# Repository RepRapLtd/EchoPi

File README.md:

# EchoPi

This is a device that uses the Raspberry Pi Zero as a WeMo device to turn on mains-powered items in your home using the Amazon Echo/Echo-Dot and their Alexa voice-recognition system.

## Safety

This uses mains electricity.  Mains will kill you if you touch it.  So don't.

The maximum current that this can switch is 1 amp.  With 220-volt mains that means a maximum 200W load; with 110-volt mains that means a maximum 100 W load.  The device is designed with a fuse holder.  Fit this with a 1 A fuse.

Parents: we set no age limits here - there are twelve-year-olds who could have organised D-Day, and there are thirty-seven-year-olds who can't be trusted with a penknife.  But don't let your children experiment with this unless you are confident that they are responsible and sensible.

Realistically, you will probably want to operate this with the cover off when you are setting it up.  Plug everything in to a disconnected extension cable and connect everything up.  Then - without touching anything to do with the uncovered case - plug the extension into a wall socket and turn it on.  Turn off and unplug the wall socket before you touch anything again.

## Electronics

The Eagle (https://cadsoft.io/) circuit design is single sided with a few jumpers.  It is intended to be produced by milling, though you can etch it conventionally as well of course.

The device incorporates a mains USB charger (like this: https://www.amazon.co.uk/Quality-Charger-Blackberry-Love-Accessories/dp/B01M2XE8V9/ ; red in the picture above).  This both acts as the plug so the device can be plugged into a wall socket, and as a 5V supply for the Raspberry Pi Zero and the rest of the electronics.

You will have to hack the charger by attaching wires to the three mains connections inside and drilling holes to run them out of.  The neutral and earth run straight through the device to the mains output, and the live wire goes through the fuse and then the opto-isolated phototriac, which switches it on and off.   

## Mechanics

The FreeCAD (http://www.freecadweb.org/) case is designed to be 3D printed.  

## Software

See here to create a linux image on an SD card for the Pi Zero:

https://www.raspberrypi.org/documentation/installation/installing-images/linux.md

Boot up the Pi Zero.  Change it's name to something you want:

http://www.howtogeek.com/167195/how-to-change-your-raspberry-pi-or-other-linux-devices-hostname/

Set your timezone:

http://www.geeklee.co.uk/update-time-zone-on-raspberry-pi-with-raspbian/

Set your Pi to have a static IP address, giving it the same one for ethernet and WiFi (you're not going to use both at once):

https://www.modmypi.com/blog/how-to-give-your-raspberry-pi-a-static-ip-address-update

Setup your WiFi network and password:

https://learn.adafruit.com/adafruits-raspberry-pi-lesson-3-network-setup/setting-up-wifi-with-occidentalis

Next get and run the EchoPi software:

$ git clone https://github.com/RepRapLtd/EchoPi.git

$ cd EchoPi/Software

$ pip install -r requirements.txt

$ nohup python echopi.py > /dev/null &

Tell Alexa, "Alexa, discover my devices."

Say, "Alexa, turn off device," and, "Alexa device on," to switch the mains socket off and on.

The line in the Python echopi.py program that sets the Alexa name of the device is this one:

     TRIGGERS = {"device": 52000}

Change the "device" to any name you like, but it's best to choose easily-pronounceable dictionary words or well-known proper nouns.  That way the Alexa speech recognition will be most reliable.

This is intended to connect to your home network using WiFi, but (particularly with BT HomeHubs) getting your Echo/Echo-Dot to find the device can be tricky.  

Start by turning off all the annoying "features" of the BT hub: disable Smart Setup; don't synchronise 5 GHz WiFi with 2.4 GHz (keep the passwords the same, though, or you'll never remember, and ignore the password warning it gives you when you do this); turn off Extended UPnP security.

Then use a micro-USB-to-ether adapter to connect the Pi Zero by wire to your hub.  

Run the Python program and tell Alexa to discover your devices.  She should find "device" (or whatever you have called it).  Test that it works by turning the load on and off.

Then shut everything down and disconnect it.  Fit a micro-USB-WiFi adapter in place of the Ethernet and power everything up again.  You should be able to ssh into the Pi as before.

Ask Alexa to turn your device on.  If she sees it, great.  But if not, press and hold the Echo/Echo-dot button to put it into set-up mode and leave it for a minute or so, then press and hold it again to turn set-up off.  It should reconnect to your hub and then be able to turn your device on and off.

The "nohup python echopi.py > /dev/null &" command will run the Python program in the background and it will stay running until you re-boot the Pi.  If you want to see what it is doing, just run "python echopi.py" instead.  But this will die when you log out.

If the program is running in the background and you want to kill it and start again, type:

$ ps -ael | grep pyth

This will give something like:

  0 S  1000   868   834 41  80   0 -  4062 poll_s pts/0    00:00:02 python

The number of the Python process is the 868.  To stop process 868 type:

$ kill -9 868

## Useful Links

Turn a Pi into an Echo/Echo-Dot equivalent:

http://www.instructables.com/id/Hacking-the-Amazon-Echo/

WeMo - the protocol used:

https://www.wemo.com/

## Acknowledgements

This is an extended fork of Todd Medema's repository here:

https://github.com/toddmedema/echo

Many thanks to him.

It uses the Raspberry Pi Zero Eagle Library from here:

https://www.raspberrypi.org/forums/viewtopic.php?f=63&t=127228

So thanks to them too.

## Licence

GPL

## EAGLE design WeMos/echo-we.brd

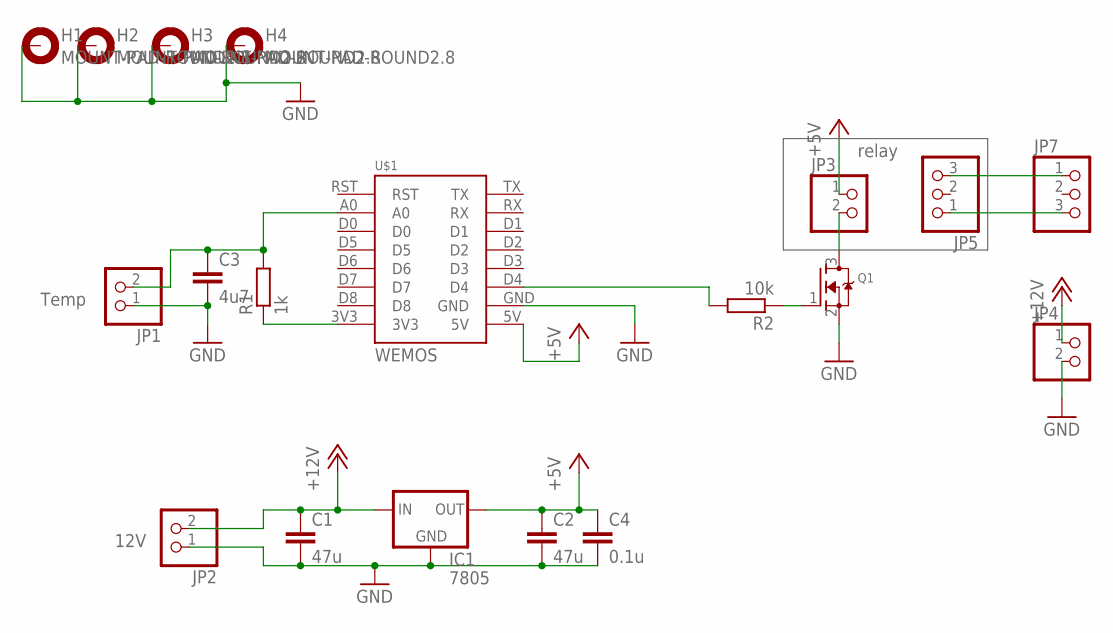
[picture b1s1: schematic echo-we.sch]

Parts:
C1, C2: 47u; C1206
C3: 4u7; C1206
C4: 0.1u; C1206
H1, H2, H3, H4: MOUNT-PAD-ROUND2.8; 2,8-PAD
IC1: 7805; 78XXS
JP1, JP2, JP3, JP4: PINHD-1X2; 1X02
JP5, JP7: PINHD-1X3; 1X03
Q1: MOSFET-NREFLOW; SOT23
R1: 1k; R0805
R2: 10k; R0805
U$1: WEMOS

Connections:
+5V: C2.1, C4.1, IC1.OUT, JP3.1, U$1.5V
+12V: C1.1, IC1.IN, JP2.2, JP4.1
GND: C1.2, C2.2, C3.2, C4.2, H1.B2,8, H2.B2,8, H3.B2,8, H4.B2,8, IC1.GND, JP1.1, JP2.1, JP4.2, Q1.2 (S), U$1.GND
unnamed: R1.1, U$1.3V3
unnamed: C3.1, JP1.2, R1.2, U$1.A0
unnamed: JP5.3, JP7.1
unnamed: JP5.1, JP7.3
unnamed: R2.2, U$1.D4
unnamed: Q1.1 (G), R2.1
unnamed: JP3.2, Q1.3 (D)

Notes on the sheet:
Temp
12V
relay

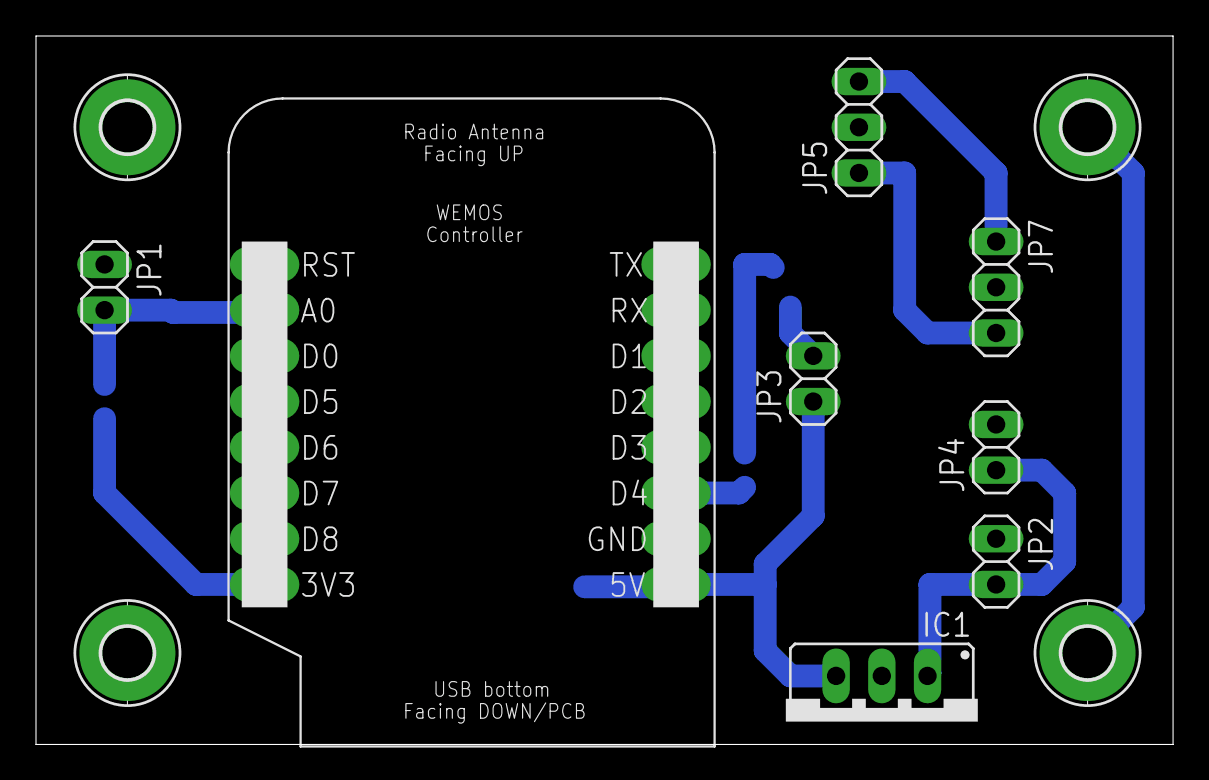
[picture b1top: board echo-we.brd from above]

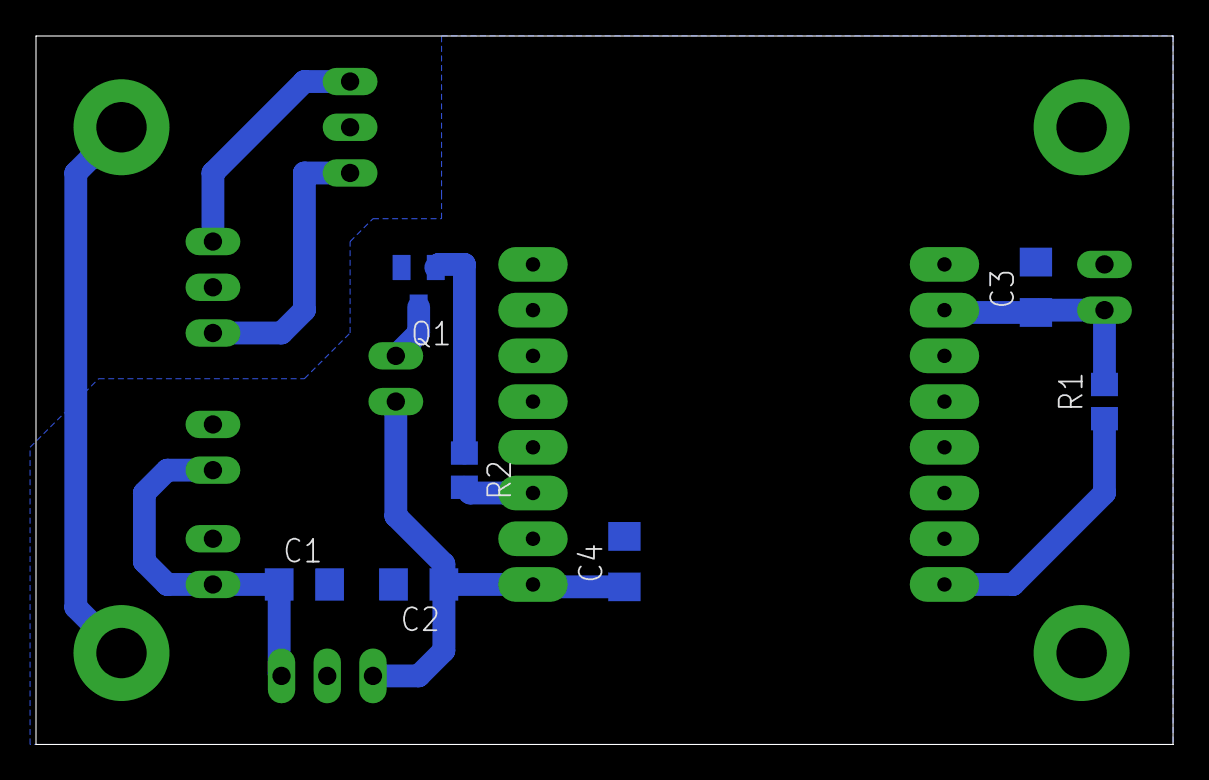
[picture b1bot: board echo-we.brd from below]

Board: 2 copper layers, 63.2 x 39.4 mm, 19 parts (7 on the bottom side), 10 nets.

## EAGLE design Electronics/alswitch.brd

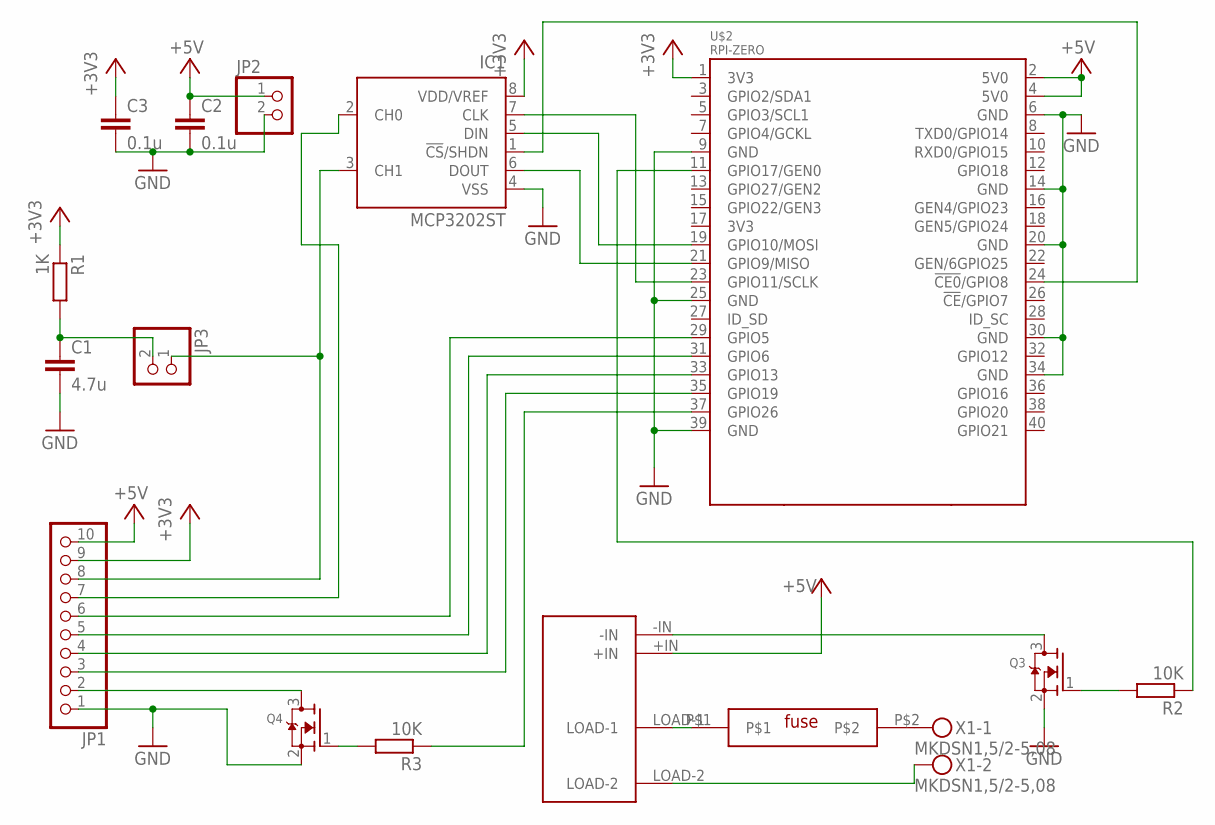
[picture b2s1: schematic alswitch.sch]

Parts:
C1: 4.7u; C1206
C2, C3: 0.1u; C1206
IC1: MCP3202ST; TSSOP8
JP1: PINHD-1X10; 1X10
JP2, JP3: PINHD-1X2; 1X02
Q3, Q4: MOSFET-NREFLOW; SOT23
R1: 1K; R0805
R2, R3: 10K; R0805
U$1: FUSE
U$2: RPI-ZERO; RASPBERRYPI_BASTELSTUBE_V13_RASPI_BOARD_B+_FULL
U$3: G3MC-201PL
X1: MKDSN1,5/2-5,08

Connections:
+3V3: C3.1, IC1.8 (VDD/VREF), JP1.9, R1.1, U$2.1 (3V3)
+5V: C2.1, JP1.10, JP2.1, U$2.2 (5V0), U$2.4 (5V0), U$3.+IN
GND: C1.2, C2.2, C3.2, IC1.4 (VSS), JP1.1, JP2.2, Q3.2 (S), Q4.2 (S), U$2.6 (GND), U$2.9 (GND), U$2.14 (GND), U$2.20 (GND), U$2.25 (GND), U$2.30 (GND), U$2.34 (GND), U$2.39 (GND)
unnamed: IC1.7 (CLK), U$2.23 (GPIO11/SCLK)
unnamed: Q3.3 (D), U$3.-IN
unnamed: R2.1, U$2.11 (GPIO17/GEN0)
unnamed: U$1.P$2, X1.1
unnamed: IC1.5 (DIN), U$2.19 (GPIO10/MOSI)
unnamed: IC1.6 (DOUT), U$2.21 (GPIO9/MISO)
unnamed: Q3.1 (G), R2.2
unnamed: JP1.6, U$2.29 (GPIO5)
unnamed: Q4.1 (G), R3.2
unnamed: JP1.3, U$2.35 (GPIO19)
unnamed: U$1.P$1, U$3.LOAD-1
unnamed: JP1.4, U$2.33 (GPIO13)
unnamed: JP1.5, U$2.31 (GPIO6)
unnamed: IC1.1 (!CS!/SHDN), U$2.24 (!CE0!/GPIO8)
unnamed: IC1.3 (CH1), JP1.8, JP3.1
unnamed: IC1.2 (CH0), JP1.7
unnamed: C1.1, JP3.2, R1.2
unnamed: JP1.2, Q4.3 (D)
unnamed: R3.1, U$2.37 (GPIO26)
unnamed: U$3.LOAD-2, X1.2

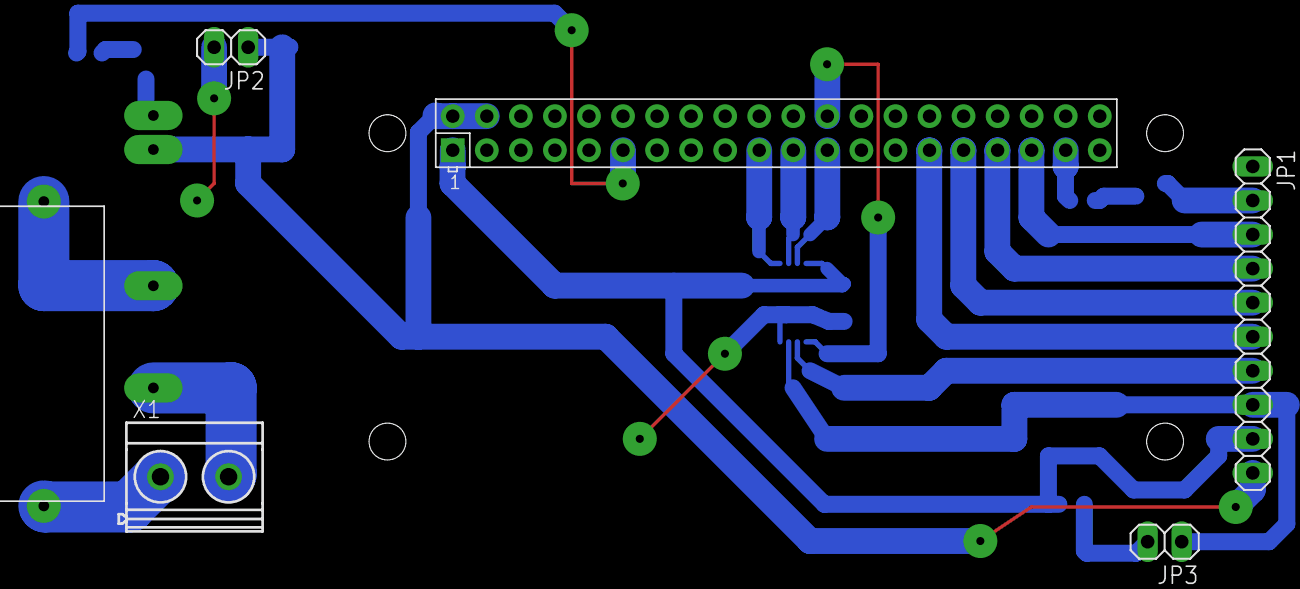
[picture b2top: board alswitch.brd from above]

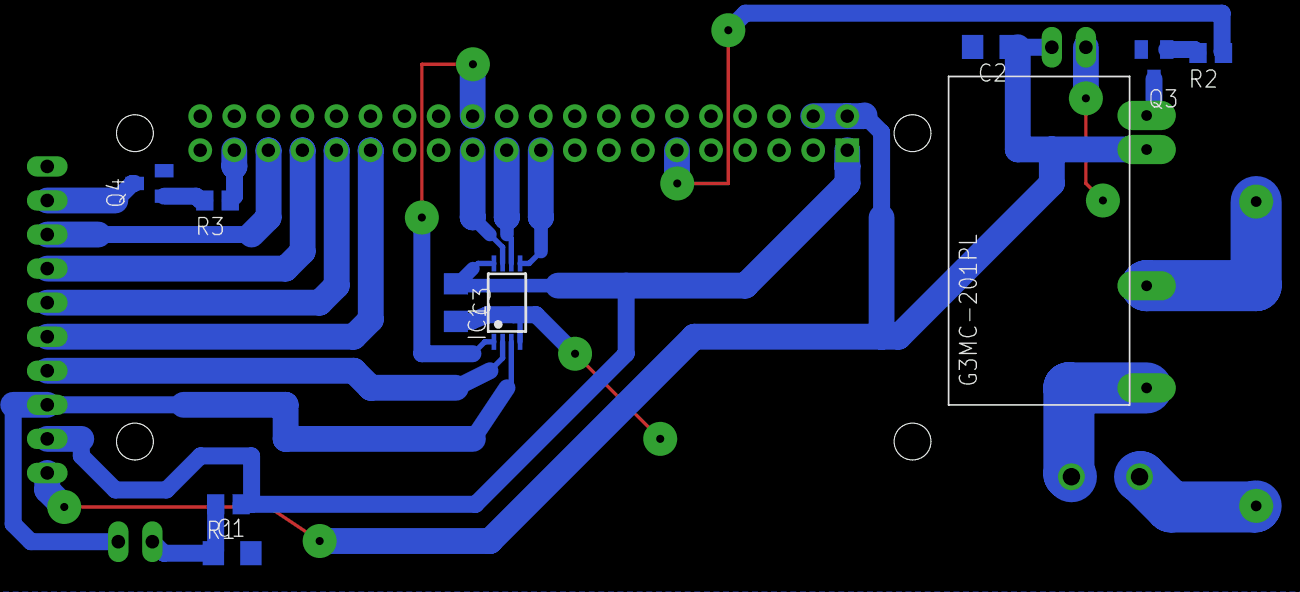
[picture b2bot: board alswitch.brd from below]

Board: 2 copper layers, 16 parts (10 on the bottom side), 23 nets.

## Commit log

2016-11-20 First commit. Added electronics and casing designs. Reorganised files.
2016-11-20 Python/Pi switche program added.
2016-11-20 README updated.
2016-11-20 CAD file tidying.
2016-11-20 Updating STL files
2016-11-20 Tidy README
2016-11-20 Pic added...
2016-11-20 Getting Pic URL right...
2016-11-20 Still getting URL right...
2016-11-20 More picture messing about
2016-11-21 Fixed my own spelling...
2016-11-21 Added link for mains charger.
2016-11-21 Thermistor holes in body added.
2016-11-22 Added more pictures.
2016-11-22 Updating STLs
2016-11-25 Small improvements to the mechanical design.
2016-11-28 Improved mechanics. Updated README.
2016-11-28 README formatting
2016-12-14 File and name tidying
2016-12-14 Added switchon.py to test the mains triac
2019-01-30 File tidying.
